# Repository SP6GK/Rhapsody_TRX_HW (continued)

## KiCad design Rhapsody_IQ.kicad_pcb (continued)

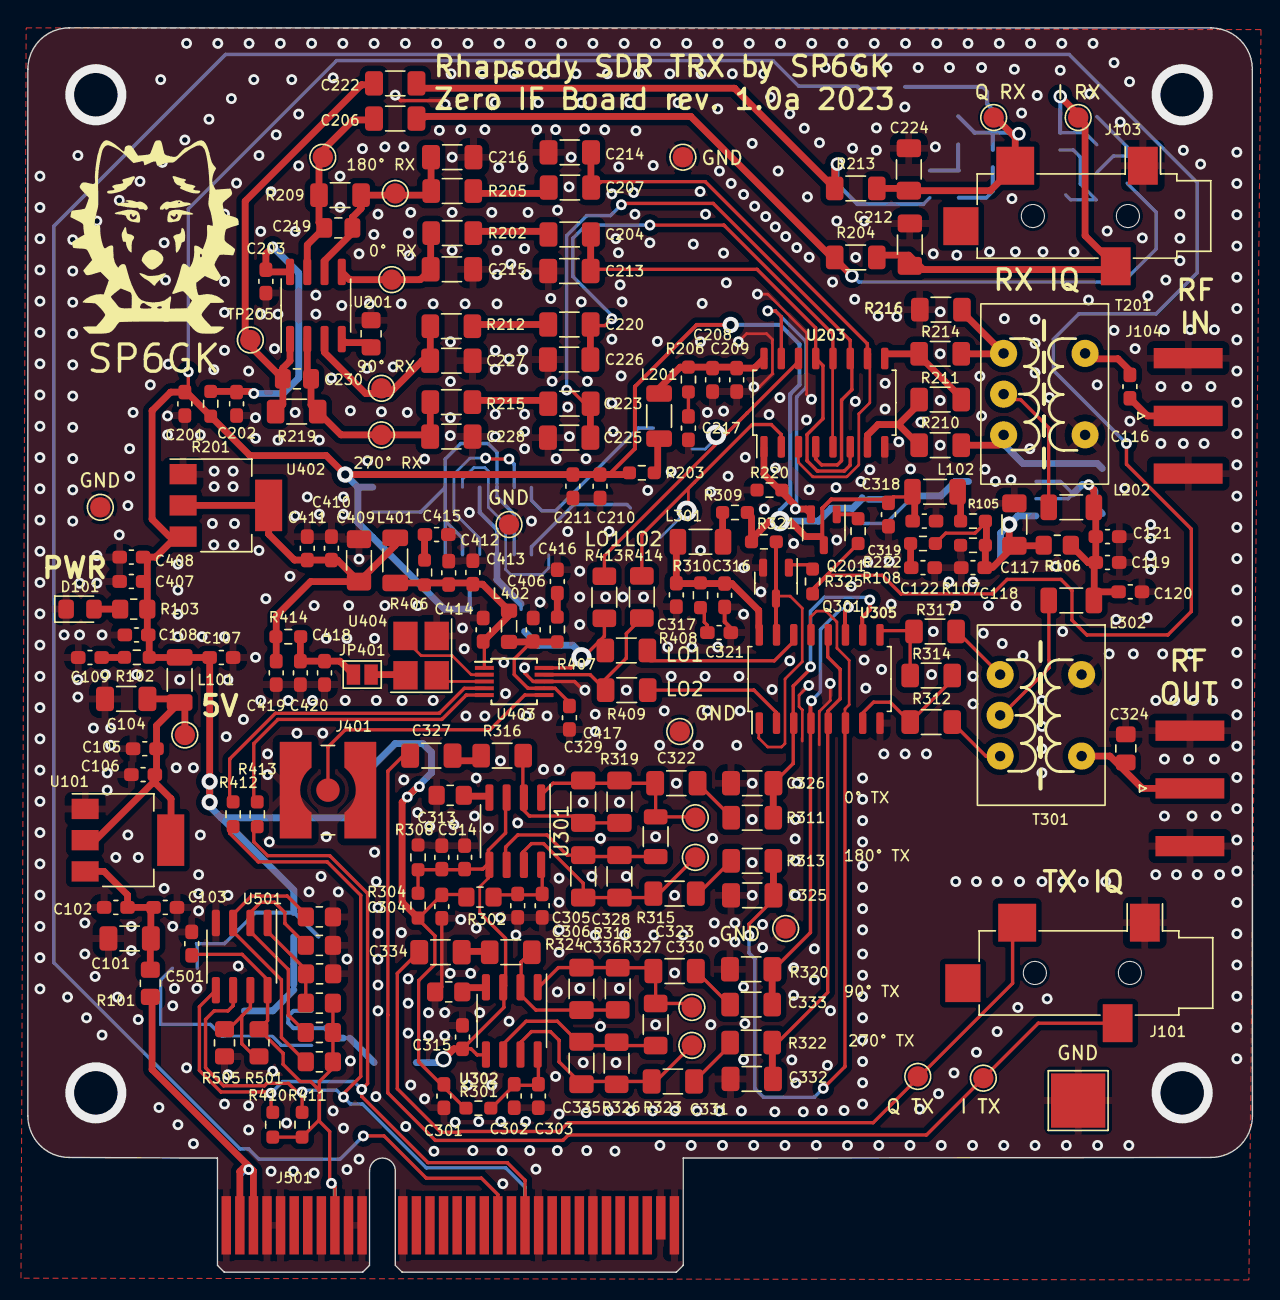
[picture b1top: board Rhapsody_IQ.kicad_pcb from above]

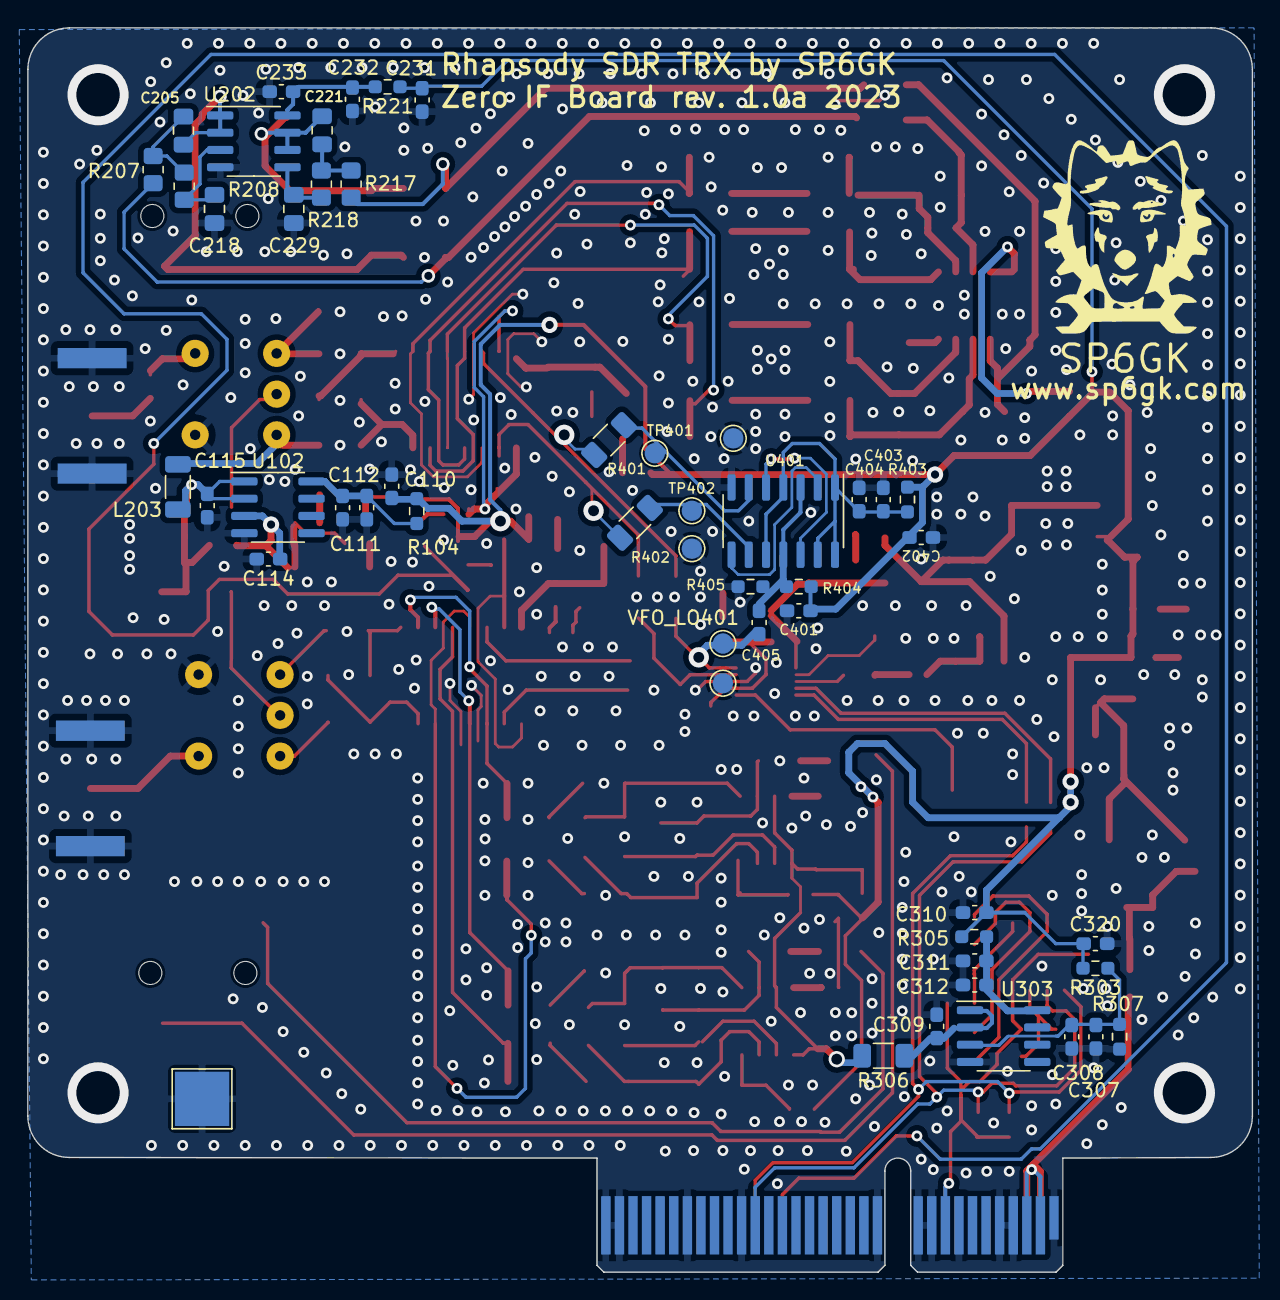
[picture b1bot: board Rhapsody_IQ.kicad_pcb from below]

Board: 2 copper layers, 90.2 x 91.6 mm, 258 parts (51 on the bottom side), 118 nets.

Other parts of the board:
R413#2: R_Small; R_0603_1608Metric_Pad0.98x0.95mm_HandSolder
R414#2: 100; R_0603_1608Metric_Pad0.98x0.95mm_HandSolder
TP108#2, TP108#3, TP108#4, TP108#5: TestPoint; TestPoint_Pad_D1.5mm

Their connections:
GND: TP108#2.1, TP108#3.1, TP108#4.1, TP108#5.1; also elsewhere on the board
